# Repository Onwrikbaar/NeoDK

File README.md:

# NeoDK
Advanced electrostimulation machine development kit.

## Overview
### What is it?
This project describes the design and implementation of a bare-bones, yet highly innovative and powerful, pulse-based electrostimulation device. Both its hardware and its firmware are open for modification and extension.

### Author
Discord: @Onwrikbaar<br/>
E: <onwrikbaar@hotmail.com>

### Status
This is a work in progress. The electronics are production-ready. The firmware is far from finished.

### Goals
1. The last quarter century, innovation in the e-stim realm has been virtually nonexistent, despite massive advances in electronics and cheap computing power. Currently available commercial devices are without exception channel-oriented and produce TENS-style waveforms. Most are horrendously energy-inefficient. The time has come to unlock the potential of a more capable architecture.
2. It is fairly easy for non-programmers to create, share and improve routines to be played on stereostim setups. Currently there is no way to achieve the same for pulse-based e-stim devices. This project aims to (eventually) bridge that gap.

### Disclaimer
NeoDK is experimental, recreational, educational hardware and software. It comes with absolutely no warranty of any kind. Its designs are free to use - under the conditions set forth in its [Licence](LICENSE.txt). Using the designs -in original or modified form- implies acceptance of any and all associated risks and liabilities.

### How to use NeoDK
- Use it entirely at your own risk.
- Keep any and all electrodes connected to this device placed below the waist.
- Always start out at low intensity, especially when using insertable electrodes.

### How NOT to use NeoDK
- Do not use it for anything safety-critical, medical, industrial, military, commercial, immoral, or illegal - it was not designed for any of that.
- Do not use it on anyone without explicit and informed consent.
- Do not use a so-called triphase cable with this device!

### Safety
NeoDK can generate potentially lethal voltages and currents on its outputs and on internal components, even when powered from a battery. The risks associated with building, testing and using this device can be reduced but not eliminated.

The NeoDK device is designed to stay within the IEC 60601-2-10 limits once its firmware is out of beta. However, these limits are not necessarily maintained when the supply voltage, circuit, components or accompanying firmware are changed in any way.

### Audience
This project is intended for experienced electronics hobbyists and professionals, who possess a keen understanding of the risks associated with electrostimulation and high-voltage circuitry, and who desire one or more of the following:
- e-stim sensations unattainable through conventional power boxes.
- a high-intensity remotely controllable e-stim device to incorporate into a multi-toy setup or home control system.
- a deeper understanding of advanced, energy-efficient electronic circuitry for pulse-based electrostimulation.
- an innovative yet compact, proven design to base one's own developments on.
- a pulse-based device that can store and play user-created routines (planned for 2026).

### Caveat
NeoDK is _NOT_ a ready-for-play e-stim box. It is a minimal viable design (MVD) of a powerful and highly efficient electrostimulation device that is not limited by 2-pole 'channels' or strictly TENS-like waveforms. Schematic and board CAD files are included, but to get a working device involves some (easy) soldering. To get more than the basic functionality requires programming in C, or being patient.

### How to get a working NeoDK
By far the easiest way to build NeoDK, is to order the SMD-populated PCB from JLCPCB (using the files in directory JLCPCB_prod) and buy the six through hole components separately. Soldering the through hole components onto the board is easy.

### Licensing
NeoDK's electronics and firmware can do things no commercially available e-stim box comes close to. If this appeals to you but you would like to have more features than NeoDK offers, by all means use NeoDK as the foundation for your own design - while observing this project's [Licence](LICENSE.txt). Regarding licensing for commercial / non-open source purposes, please contact the author.

### Why to start simple
"A complex system that works is invariably found to have evolved from a simple system that worked. A complex system designed from scratch never works and cannot be patched up to make it work. You have to start over with a working simple system." -- John Gall

## NeoDK in the media
Joanne's Reviews' always informative and entertaining YouTube [E-stim Livestreams](https://www.youtube.com/@JoannesReviews/streams) recently featured an [item about NeoDK](https://youtu.be/giEaDksRmh0?t=1460).

## Other OSHW electrostimulation projects
- [zc95](https://github.com/CrashOverride85/zc95). A feature-rich four channel machine.
- [FOC-Stim](https://github.com/diglet48/FOC-Stim). Highly innovative, quickly rendering stereostim obsolete.
- Noisy Cricket (soon to be published). An incredibly compact device primarily aimed at BDSM play.

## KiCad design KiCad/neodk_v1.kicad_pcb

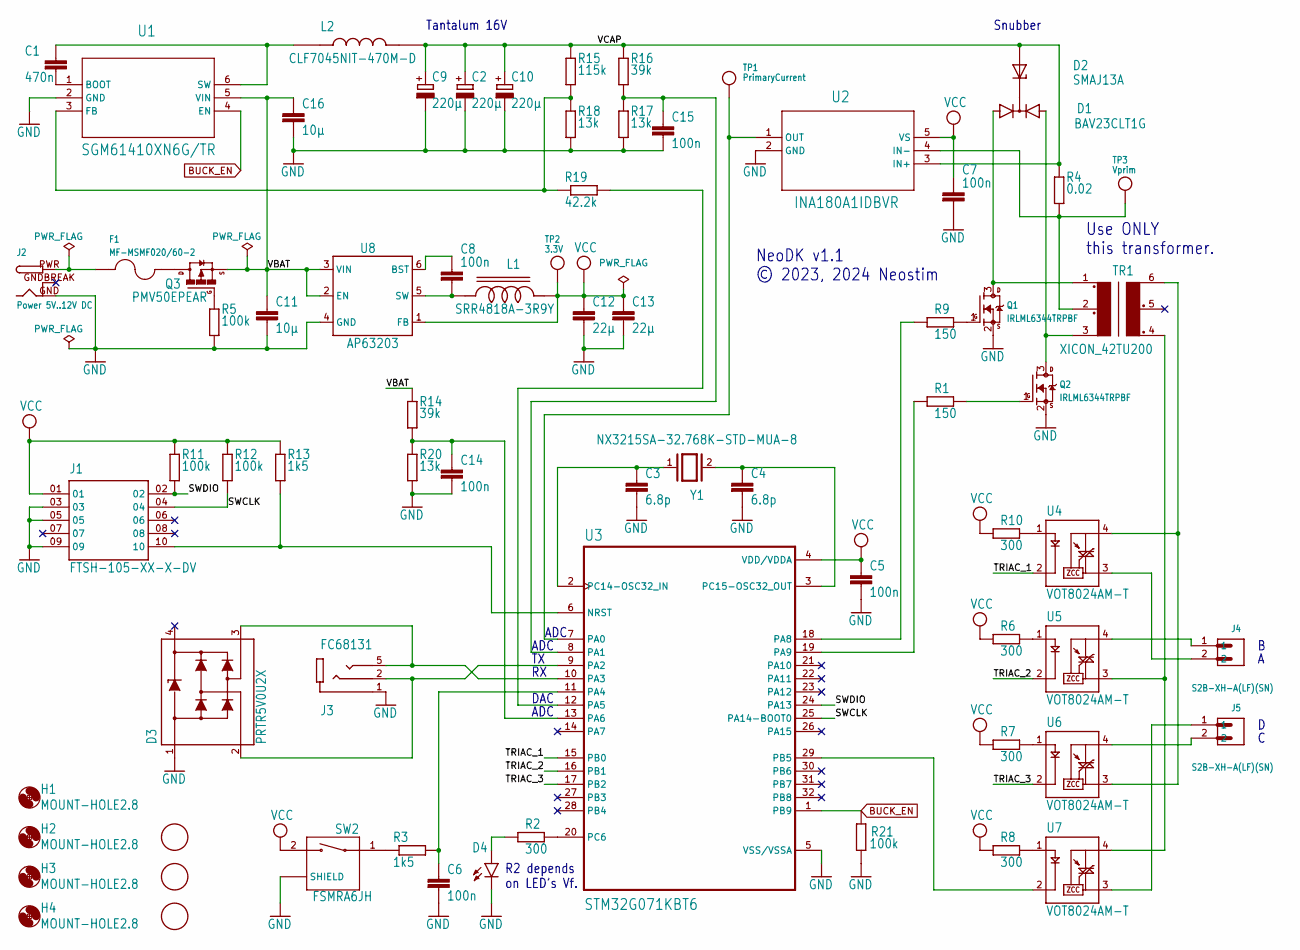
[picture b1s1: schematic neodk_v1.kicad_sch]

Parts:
C1: 470n; C0603
C2, C9, C10: 220µ; SMC_D
C3, C4: 6.8p; C0603
C5, C6, C7, C8, C14, C15: 100n; C0603
C11, C16: 10µ; C0603
C12, C13: 22µ; C0603
D1: BAV23CLT1G; SOT23
D2: SMAJ13A; DIOM4325X250N
D3: PRTR5V0U2X; SOT190P230X110-4N
D4: LEDCHIP-LED0805; CHIP-LED0805
F1: MF-MSMF020/60-2; FUSER_MF-MSMF020_60-2
FID1, FID2, FID3: FIDUCIAL; FIDUCIAL_1MM
H1, H2, H3, H4: MOUNT-HOLE2.8; 2,8
J1: FTSH-105-XX-X-DV; SAMTEC_FTSH-105-XX-X-DV
J2: Power 5V..12V DC; DCJACK_2MM_PTH
J3: FC68131; CLIFF_FC68131
J4, J5: S2B-XH-A(LF)(SN); JST_S2B-XH-A(LF)(SN)
L1: SRR4818A-3R9Y; IND_SRR4818A-3R9Y
L2: CLF7045NIT-470M-D; IND_CLF7045NIT-470M-D
Q1, Q2: IRLML6344TRPBF; SOT23
Q3: PMV50EPEAR; SOT23
R1, R9: 150; R0603
R2, R6, R7, R8, R10: 300; R0603
R3, R13: 1k5; R0603
R4: 0.02; R1206
R5, R11, R12, R21: 100k; R0603
R14, R16: 39k; R0603
R15: 115k; R0603
R17, R18, R20: 13k; R0603
R19: 42.2k; R0603
SW2: FSMRA6JH; TE_FSMRA6JH
TP1: PrimaryCurrent; TESTPOINT_ROUND_1MM
TP2: 3.3V; TESTPOINT_ROUND_1MM
TP3: Vprim; TESTPOINT_ROUND_1MM
TR1: XICON_42TU200; 42TUXXX
U1: SGM61410XN6G/TR; SOT-23-6_SNC
U2: INA180A1IDBVR; DBV5
U3: STM32G071KBT6; QFP80P900X900X160-32N
U4, U5, U6, U7: VOT8024AM-T; SOP254P675X240-4N
U8: AP63203; SOT23-6
Y1: NX3215SA-32.768K-STD-MUA-8; XTAL_NX3215SA-32.768K-STD-MUA-8

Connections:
BTN_OUT1: C6.1, R3.2, U3.11 (PA4)
BUCK_EN: R21.2, U1.4 (EN), U3.1 (PB9)
CSA_OUT: TP1.P$1, U2.1 (OUT), U3.7 (PA0)
GND: C2.-, C3.2, C4.2, C5.2, C6.2, C7.2, C9.-, C10.-, C11.2, C12.2, C13.2, C14.2, C15.2, C16.2, D3.1 (GND), D4.C, J1.03, J1.05, J1.09, J2.GND, J3.1 (SLEEVE), Q1.2 (S), Q2.2 (S), R5.1, R17.1, R18.1, R20.1, R21.1, SW2.S1 (SHIELD), SW2.S2 (SHIELD), U1.2 (GND), U2.2 (GND), U3.5 (VSS/VSSA), U8.4 (GND)
GNDBREAK: J2.GNDBREAK
unnamed: D1.3 (C), D2.C
unnamed: R3.1, SW2.1
unnamed: D1.1 (A1), Q1.3 (D), TR1.1
unnamed: D1.2 (A2), Q2.3 (D), TR1.3
unnamed: Q1.1 (G), R9.2
unnamed: Q2.1 (G), R1.2
unnamed: R2.2, U3.20 (PC6)
unnamed: D4.A, R2.1
unnamed: R4.1, TP3.P$1, TR1.2, U2.4 (IN-)
unnamed: R10.1, U4.1 (A)
unnamed: R6.1, U5.1 (A)
unnamed: R7.1, U6.1 (A)
unnamed: J4.1, U5.4 (MT2)
unnamed: R8.1, U7.1 (A)
unnamed: R1.1, U3.19 (PA9)
unnamed: U3.29 (PB5), U7.2 (C)
unnamed: J5.2, U6.4 (MT2)
unnamed: TR1.4, U5.3 (MT1), U7.4 (MT2)
unnamed: R9.1, U3.18 (PA8)
unnamed: TR1.6, U4.4 (MT2), U6.3 (MT1)
unnamed: J4.2, U4.3 (MT1)
unnamed: J5.1, U7.3 (MT1)
unnamed: C4.1, U3.3 (PC15-OSC32_OUT), Y1.2
unnamed: C3.1, U3.2 (PC14-OSC32_IN), Y1.1
unnamed: D3.3 (I/O_2), J3.5 (TIP), U3.10 (PA3)
unnamed: F1.1, J2.PWR
unnamed: D3.2 (I/O_1), J3.2 (RING), U3.9 (PA2)
unnamed: F1.2, Q3.2 (D)
unnamed: Q3.1 (G), R5.2
unnamed: C1.1, L2.1, U1.6 (SW)
unnamed: C1.2, U1.1 (BOOT)
unnamed: C14.1, R14.1, R20.2, U3.13 (PA6)
unnamed: C8.2, L1.1, U8.5 (SW)
unnamed: C8.1, U8.6 (BST)
unnamed: R15.1, R18.2, R19.1, U1.3 (FB)
unnamed: R19.2, U3.12 (PA5)
unnamed: J1.10, R13.1, U3.6 (NRST)
SWCLK: J1.04, R12.1, U3.25 (PA14-BOOT0)
SWDIO: J1.02, R11.1, U3.24 (PA13)
TRIAC_1: U3.15 (PB0), U4.2 (C)
TRIAC_2: U3.16 (PB1), U5.2 (C)
TRIAC_3: U3.17 (PB2), U6.2 (C)
VBAT: C11.1, C16.1, Q3.3 (S), R14.2, U1.5 (VIN), U8.2 (EN), U8.3 (VIN)
VCAP: C2.+, C9.+, C10.+, D2.A, L2.2, R4.2, R15.2, R16.2, U2.3 (IN+)
VCC: C5.1, C7.1, C12.1, C13.1, J1.01, L1.2, R6.2, R7.2, R8.2, R10.2, R11.2, R12.2, R13.2, SW2.2, TP2.P$1, U2.5 (VS), U3.4 (VDD/VDDA), U8.1 (FB)
VC_DIV4: C15.1, R16.1, R17.2, U3.8 (PA1)

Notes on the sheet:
Tantalum 16V
Snubber
ADC
R2 depends on LED's Vf.
NeoDK v1.1 © 2023, 2024 Neostim
Use ONLY this transformer.
DAC

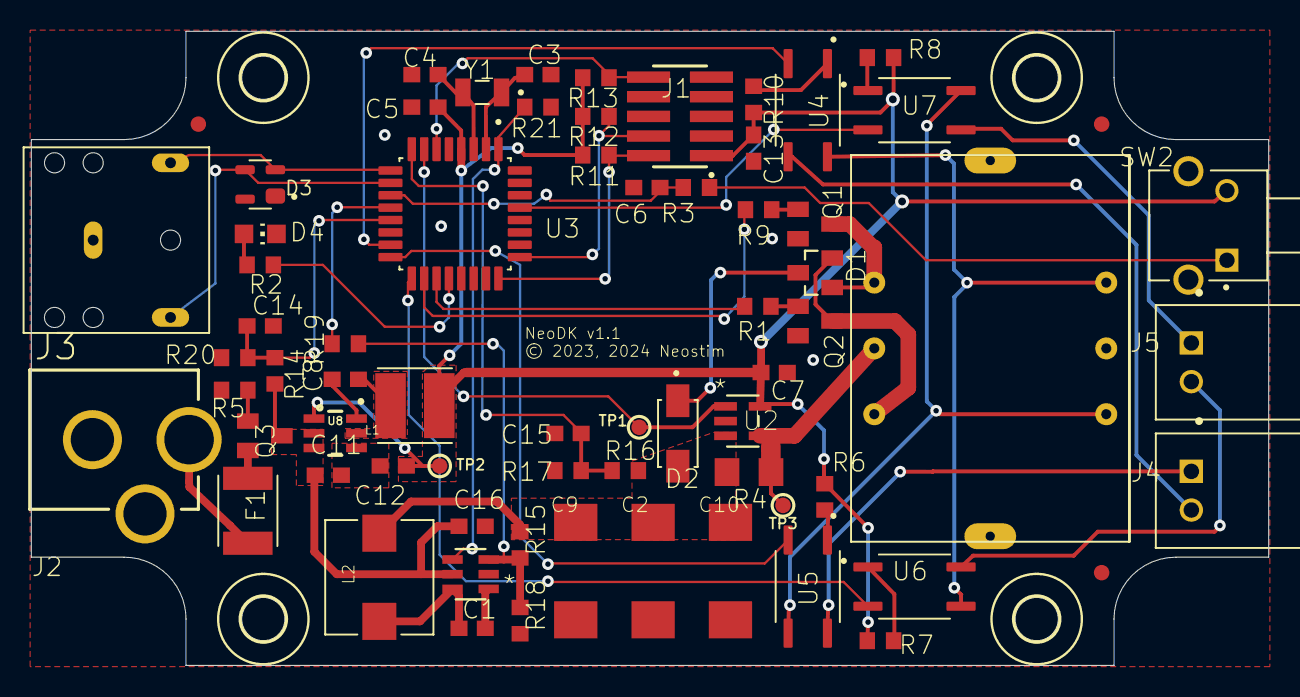
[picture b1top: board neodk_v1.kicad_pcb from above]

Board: 2 copper layers, 80.0 x 41.0 mm, 73 parts (0 on the bottom side), 50 nets.

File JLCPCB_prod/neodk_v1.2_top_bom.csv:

Comment,Designator,Footprint,LCSC Part #,
0.02,R4,R1206,
1k5,R3 R13,R0603,
VLS5045EX-4R7M,L1,IND_VLS5045EX-4R7M,
6.8p,C3 C4,C0603,
10u,C11 C16,C0603,
13k,R17 R18 R20,R0603,
22u,C12 C13,C0603,
X1A0001410003,Y1,SMD3215-2P,
39k,R14 R16,R0603,
42.2k,R19,R0603,
CLF7045NIT-470M-D,L2,IND_CLF7045NIT-470M-D,
100k,R5 R11 R12 R21,R0603,
100n,C5 C6 C7 C8 C14 C15,C0603,
115k,R15,R0603,
150,R1 R9,R0603,
T491X227K016AT,C2 C9 C10,SMC_D,
300,R2 R6 R7 R8 R10,R0603,
470n,C1,C0603,
AP63203WU-7,U8,SOT23-6,
BAV23CLT1G,D1,SOT23,
INA180A1IDBVR,U2,DBV5,
IRLML6344TRPBF,Q1 Q2,SOT23,
MF-MSMF020/60-2,F1,FUSER_MF-MSMF020/60-2,
PMV50EPEAR,Q3,SOT23,
PRTR5V0U2X,D3,SOT-143,
SGM61410XN6G(TOKMAS),U1,SOT-23-6_SNC,
SMAJ13A,D2,SMA,
SZYY0805B,D4,0805,C434433,
STM32G071KBT6,U3,QFP80P900X900X160-32N,
20021121-00010T4LF,J1,20021121-00010T4LF,
TLP268J,U4 U5 U6 U7,SOP254P675X240-4N,

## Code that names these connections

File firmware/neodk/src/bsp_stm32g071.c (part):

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#define MOSFET_2_PIN            LL_GPIO_PIN_9   // Digital out, push-pull.

#define TRIAC_GPIO_PORT         GPIOB
#define TRIAC_1_PIN             LL_GPIO_PIN_0   // Digital out, open drain.
#define TRIAC_2_PIN             LL_GPIO_PIN_1   // Digital out, open drain.
#define TRIAC_3_PIN             LL_GPIO_PIN_2   // Digital out, open drain.
#define TRIAC_4_PIN             LL_GPIO_PIN_5   // Digital out, open drain.
#define ALL_TRIAC_PINS          (TRIAC_1_PIN | TRIAC_2_PIN | TRIAC_3_PIN | TRIAC_4_PIN)

#define BUCK_GPIO_PORT          GPIOB
#define BUCK_ENABLE_PIN         LL_GPIO_PIN_9   // Digital out, push-pull.
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
    // The triac enable signals are active low.
    TRIAC_GPIO_PORT->BSRR
        = (pattern & 1 ? TRIAC_1_PIN << 16 : TRIAC_1_PIN)
        | (pattern & 2 ? TRIAC_2_PIN << 16 : TRIAC_2_PIN)
        | (pattern & 4 ? TRIAC_3_PIN << 16 : TRIAC_3_PIN)
        | (pattern & 8 ? TRIAC_4_PIN << 16 : TRIAC_4_PIN);
}

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
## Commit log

2023-08-17 Specifications.
2023-08-19 Added partial schematic.
2023-08-21 Use triac with 5 mA input current to trigger
2023-09-04 Vcap regulation and 3.3V buck.
2023-09-20 Updated schematic, and more.
2023-10-07 Board place & route done.
2023-10-21 Initial firmware: blinky.
2023-10-21 Pushbutton works too.
2023-10-21 Don't track binaries.
2023-11-27 First board.
2023-12-03 Generate pulses.
2023-12-26 More firmware and Eagle board file.
2024-01-03 Bug fix and minor stuff.
2024-02-27 Prep for serial comms and pulse sequencer.
2024-02-27 Mostly refactoring.
2024-03-05 Added pattern sequencer.
2024-03-15 Pattern sequencer and comms logic.
2024-03-26 Refactoring, mostly.
2024-05-07 Updated schematic and board.
2024-05-09 Add KiCad project. Board not checked!
2024-05-09 Event queues for the state machines.
2024-06-03 Added CSV for Toggle routine.
2024-08-09 Added feature to switch to bootloader.
2024-08-10 Pics of V1.2 schematic and board layout.
2024-08-11 Catch ADC event in pulsing state.
2024-08-16 Added production files for JLCPCB.
2024-08-19 Always turn on the output stage.
2024-08-20 Reduced quiescent current.
2024-08-21 Comms prep for remote commands.
2024-08-22 More remote commands prep.
2024-08-23 Add CAD files for enclosure panels.
2024-08-23 New CAD files for enclosure panels.
2024-08-30 Fixed subtle pulse timing bug.
2024-09-10 UI prep.
2024-09-11 Further UI prep.
2024-09-12 Basic control through serial port.
2024-09-13 Use more interesting default pattern.
2024-09-21 Reorganised setup instructions.
2024-09-22 Add build automation via Github Actions
2024-09-23 Change repetition rate of the default pattern.
2024-09-25 Update workflow to use variables.
    This fixes an invalid-path issue if a cloned repository uses a different name.
2024-09-28 Production files for hardware v1.3.
2024-10-01 Add /n command to select next routine.
2024-10-05 Added (default) pattern for mixed impedance electrodes.
2024-10-08 Lower initial voltage and pulse width. Also minor refactoring.
2024-10-09 Some API prep.
2024-10-10 More API prep.
2024-10-11 Controller interaction boilerplate.
2024-10-13 Reorganising.
2024-10-14 Prep for Dweeb.
2024-10-15 Basic event subscription mechanism.
2024-10-16 Ready for Dweeb.
2024-10-19 Cosmetics.
2024-10-20 Comms PAR algorithm prep.
2024-11-13 Added link to @edger477's UI in Setup.md.
2024-11-19 first version of js api and UI based on it
2024-11-20 Allow read of virtual attributes.
2024-11-20 added battery voltage
2024-11-20 Update static.yml
    to deploy only UI
2024-11-20 Let client set the name of the box.
2024-11-20 added box name support
2024-11-20 Allow reading the firmware version attribute.
2024-11-21 New pattern, slightly more superficial.
2024-11-23 If any patterns are bad, do not allow pulse generation.
2024-11-29 Use fuse that is in stock at JLC.
2024-12-07 Fixed pulse width bug.
2024-12-18 Fixed typo.
2024-12-28 Pulse train streaming prep and some refactoring.
2024-12-29 Rudimentary pulse train streaming.
2025-01-06 Small changes to the pulse train descriptor format.
2025-01-07 Pulse train queue and bug fix.
2025-01-10 Refactoring & smaller pulse train descriptor.
2025-01-10 Some pulse train stream handling.
2025-01-11 Some serious refactoring.
2025-01-12 Further pulse train streaming preparation.
2025-01-13 Improved pulse train queueing.
2025-01-14 More stream handling.
2025-01-17 Free the 32-bit timer for use by the sequencer.
2025-01-22 Pulse train streaming 🆗
2025-01-28 Infrastructure, mostly.
2025-02-04 More sequencer logic.
2025-02-04 Correct hex file.
2025-02-04 Fewer inconsistencies.
2025-02-07 Temporarily removed lower limit on pulse pace, for research purposes.
2025-02-08 Adjust timing of last pulse in streamed burst.
2025-02-08 Minor refactoring.
2025-02-22 Bug fixes and minor changes.
2025-02-23 Some Restim adaptations.
2025-02-24 Added writable heartbeat interval attribute.
2025-02-24 Experimental feature for @diglet.
2025-02-24 Extra timing check.
2025-02-26 Switch triacs earlier.
2025-02-28 Document the pulse train descriptor.
2025-03-01 Single-pulse streaming subtleties.
2025-03-02 Short-pulse triac timing fix.
2025-03-04 Update pulse timer shadow registers shortly before enable.
2025-03-05 Minor burst event shuffling.
2025-03-21 Updated BoM for availability.
2025-04-02 Trigger ADC during each pulse.
2025-04-05 Refactoring for modularity.
2025-05-29 Ensure JLC places the correct FETs.
2025-05-30 Update neodk.js
    Added support for HC-05 and HC-06 Bluetooth serial modules.
2025-10-23 Only set intensity to default on pattern switch when it is higher.
2025-12-02 No functional changes.
2025-12-29 Bug fixes & improved pulse train streaming.
2025-12-29 Undo mistake.
2026-01-08 Comms bug fix & minor refactoring.

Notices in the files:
firmware/neodk/src/bsp_stm32g071.c:
Copyright  2023..2026 Neostim™
